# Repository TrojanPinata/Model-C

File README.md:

<div align="center">

# Model-C

### A four function calculator and numpad combo with integrated battery, power-saving, and mechanical switches

The first version of this project is stored in the `old pcb` directory, and is based off of the ATmega32A MCU. While good, I felt like the RP2040 is more realistic in terms of both cost and development overhead.

</div>

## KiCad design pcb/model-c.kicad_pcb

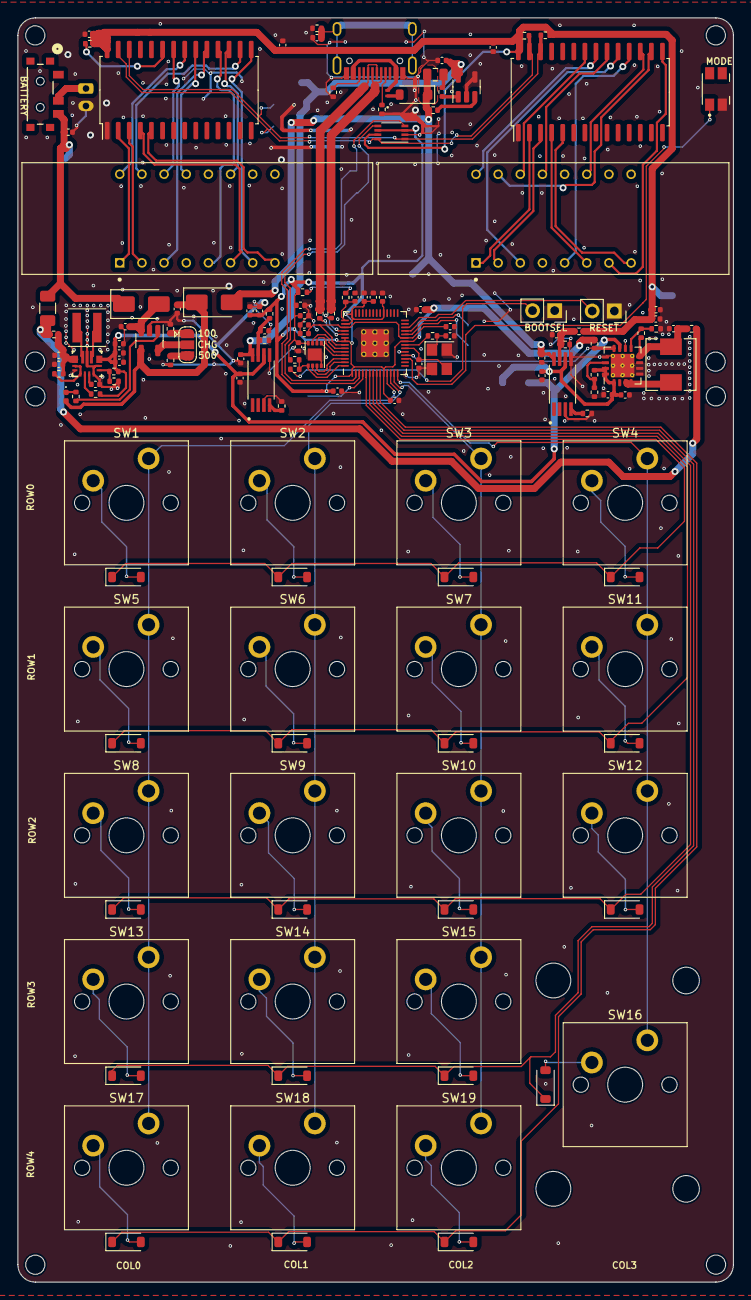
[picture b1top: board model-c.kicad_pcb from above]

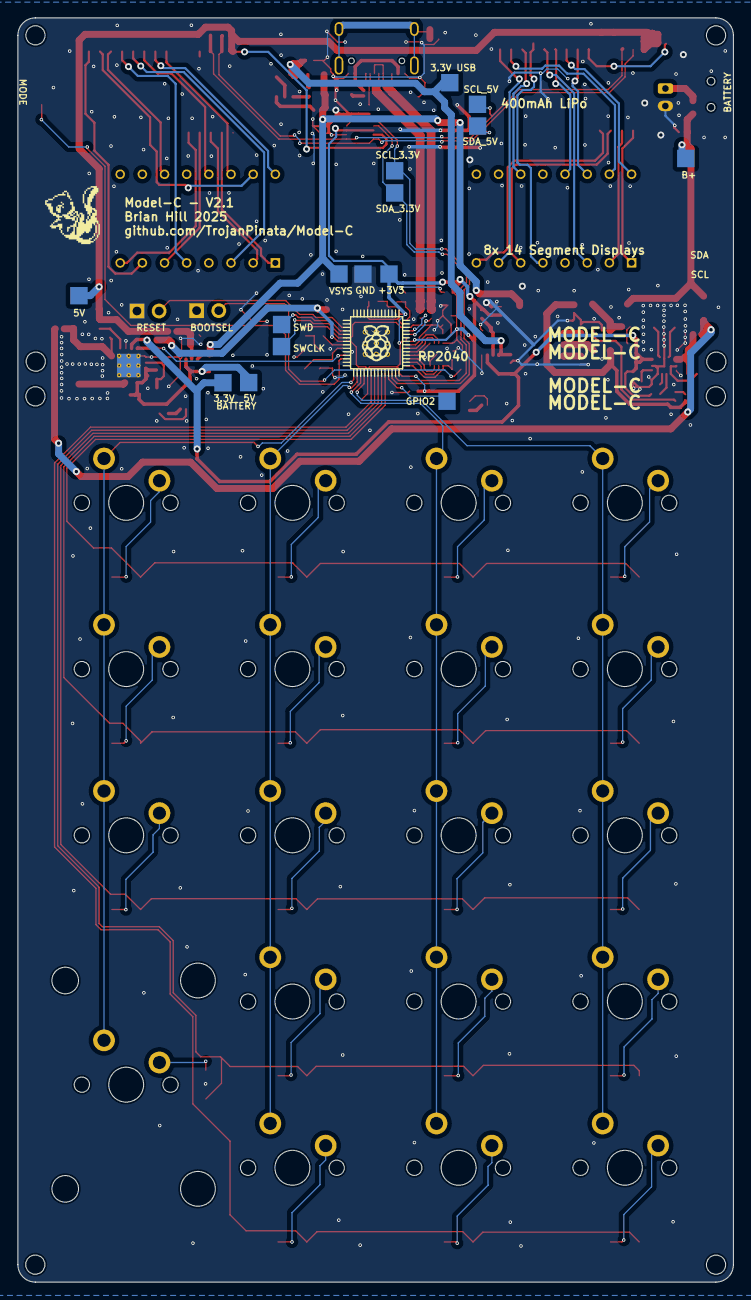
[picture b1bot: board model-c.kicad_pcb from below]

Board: 2 copper layers, 82.0 x 144.9 mm, 161 parts (16 on the bottom side), 120 nets.

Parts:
C1, C5, C6, C8, C9, C11, C12, C13, C14, C15, C16, C17, C24, C30, C31, C32, C33: 0.1uF; C_0402_1005Metric
C2, C21, C23, C25, C26, C29, C34, C37, C39, C40, C41: 10uF; C_0402_1005Metric
C3, C4: 22pF; C_0402_1005Metric
C7, C42: 1uF; C_0402_1005Metric
C10, C18: 2.2uF; C_0402_1005Metric
C19, C20, C22: 4.7uF; C_0402_1005Metric
C27, C35, C36: 22uF; C_0402_1005Metric
C28: 100uF_LowESR; C_0402_1005Metric
C38: 100nF; C_0402_1005Metric
D1, D2, D3, D4, D5, D6, D7, D8, D9, D10, D11, D12, D13, D14, D15, D16, D17, D18, D19: D; D_SOD-123
D21: 1N4002W; D_SOD-123
D22: MBRA140; D_SMA
D23: LED; LED_0402_1005Metric
D24: SS14; D_SMA
D25: TPD1E05U06; RTVS_DFN1006-2_SOD882_NEX
DS1, DS2: TDCG1060M; DISPLAY_TDCG1060M
F1: 0805L050WR; Fuse_0805_2012Metric
F2: MF-NSMF075-2; Fuse_1206_3216Metric
FB1, FB2, FB3, FB4, FB5: FB; R_0402_1005Metric
H1: Stabilizer; Stabilizer_Cherry_MX_2.00u
IC1, IC2: HTK16K33; SOP-28_7.5x17.9mm_P1.27mm
J1: Batt; JST_PH_S2B-PH-K_1x02_P2.00mm_Horizontal
J2, J3: Conn_01x02_Socket; PinSocket_1x02_P2.54mm_Vertical
JP2: 500mA - 100mA; SolderJumper-3_P1.3mm_Open_RoundedPad1.0x1.5mm
L1: 4.7uH; L_Sunlord_MWSA0503S
L2: 1.5uH; L_Coilcraft_XxL4020
R1, R3: 1k; R_0402_1005Metric
R2, R8, R16, R21, R23: 10k; R_0402_1005Metric
R4: 47k; R_0402_1005Metric
R5: 160k; R_0402_1005Metric
R6, R7: 5.1k; R_0402_1005Metric
R9, R22, R26, R27, R28, R30, R32: 100k; R_0402_1005Metric
R10: 200; R_0402_1005Metric
R11: 1; R_0402_1005Metric
R12, R13: 27; R_0402_1005Metric
R14: 330; R_0402_1005Metric
R15: 2k; R_0402_1005Metric
R24, R25, R33, R34: 4.7k; R_0402_1005Metric
R29: 316k; R_0402_1005Metric
R31: 523k; R_0402_1005Metric
S1: MODE; SW_EVQ-P7A01P
SW1, SW2, SW3, SW4, SW5, SW6, SW7, SW8, SW9, SW10, SW11, SW12, SW13, SW14, SW15, SW17, SW18, SW19: SW_SPST; SW_Cherry_MX_PCB_1.00u
SW16: SW_SPST; SW_Cherry_MX_PCB_2.00u_90deg
SW21: SW_SPDT; MK-12C02-G020_GSW
TP1, TP2, TP3, TP4, TP5, TP6, TP7, TP8, TP9, TP10, TP11, TP12, TP13, TP14, TP15: TestPoint; CustomTestPoint
U1: W25Q16JVUXIQ; SON-8-1EP_3x2mm_P0.5mm_EP1.4x1.6mm
U3: RP2040; RP2040-QFN-56
U4: MCP73831-2-OT; SOT-23-5
U5: TPS61090; Texas_S-PVQFN-N16_EP2.7x2.7mm_ThermalVias
U7: TLV75533PDBVR; SOT-23-5
U8, U9: TPS2115APW; SOP65P640X120-8N
U10: TXS0102DCU; VSSOP-8_2.3x2mm_P0.5mm
U11: TPS63070RNMR; RNM0015A
USB1: HRO-TYPE-C-31-M-12
Y1: 12MHz; Crystal_SMD_3225-4Pin_3.2x2.5mm

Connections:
+1V1: C7.1, C8.1, C9.1, U3.23 (DVDD), U3.45 (VREG_VOUT), U3.50 (DVDD)
+3V3: C1.2, C2.1, C11.1, C12.1, C13.1, C14.1, C15.1, C16.1, C17.1, C18.1, C22.1, FB3.1, R2.2, R10.1, R21.1, TP9.1, U1.8 (VCC), U3.1 (IOVDD), U3.10 (IOVDD), U3.22 (IOVDD), U3.33 (IOVDD), U3.42 (IOVDD), U3.44 (VREG_IN), U3.48 (USB_VDD), U3.49 (IOVDD), U10.3 (VCCA), U10.6 (OE)
+5V: C5.1, C21.1, C23.1, C24.1, C25.1, FB2.1, IC1.28 (VDD), IC2.28 (VDD), R4.2, R33.1, R34.2, TP11.1, U10.7 (VCCB)
/3.3V_BATT: C30.1, C39.2, C40.1, C41.2, R28.1, R29.1, TP10.1, U5.11 (EN), U8.6 (1N2), U11.7 (VOUT), U11.8 (VOUT)
/3.3V_USB: C29.1, C31.1, TP7.1, U7.5 (OUT), U8.8 (1N1)
/5V_BATT: C27.1, C28.1, C33.1, R31.2, TP8.1, U5.1 (VOUT), U5.15 (VOUT), U5.16 (VOUT), U9.6 (1N2)
/ADC_VREF: R10.2, R11.1
/B+: F2.2, FB4.2, FB5.2
/LBO: R21.2, U3.18 (GPIO15), U5.12 (LBO)
/QSPI_SCLK: U1.6 (CLK), U3.52 (QSPI_SCLK)
/QSPI_SD0: U1.5 (DI(IO0)), U3.53 (QSPI_SD0)
/QSPI_SD1: U1.2 (DO(IO1)), U3.55 (QSPI_SD1)
/QSPI_SD2: U1.3 (IO2), U3.54 (QSPI_SD2)
/QSPI_SD3: U1.7 (IO3), U3.51 (QSPI_SD3)
/QSPI_SS: R1.1, R2.1, U1.1 (~CS), U3.56 (QSPI_SS)
/RUN: J3.2, U3.26 (RUN)
/SCL_3.3V: TP15.1, U3.3 (GPIO1), U10.4 (A2)
/SCL_5V: IC1.26 (SCL), IC2.26 (SCL), R33.2, TP12.1, U10.1 (B2)
/SDA_3.3V: TP14.1, U3.2 (GPIO0), U10.5 (A1)
/SDA_5V: IC1.27 (SDA), IC2.27 (SDA), R34.1, TP13.1, U10.8 (B1)
/USB_BOOT: J2.2, R1.2
/USB_DN: R13.2, USB1.5 (DN2), USB1.7 (DN1)
/USB_DP: R12.2, USB1.6 (DP1), USB1.8 (DP2)
/XIN: C3.2, U3.20 (XIN), Y1.3
/XOUT: R3.2, U3.21 (XOUT)
/col0: SW1.2 (B), SW5.2 (B), SW8.2 (B), SW13.2 (B), SW17.2 (B), U3.11 (GPIO8)
/col1: SW2.2 (B), SW6.2 (B), SW9.2 (B), SW14.2 (B), SW18.2 (B), U3.12 (GPIO9)
/col2: SW3.2 (B), SW7.2 (B), SW10.2 (B), SW15.2 (B), SW19.2 (B), U3.13 (GPIO10)
/col3: SW4.2 (B), SW11.2 (B), SW12.2 (B), SW16.2 (B), U3.14 (GPIO11)
/mode: S1.1_1, U3.17 (GPIO14)
/row0: D1.1 (K), D2.1 (K), D3.1 (K), D4.1 (K), U3.5 (GPIO3)
/row1: D5.1 (K), D6.1 (K), D7.1 (K), D8.1 (K), U3.6 (GPIO4)
/row2: D9.1 (K), D10.1 (K), D11.1 (K), D12.1 (K), U3.7 (GPIO5)
/row3: D13.1 (K), D14.1 (K), D15.1 (K), D16.1 (K), U3.8 (GPIO6)
/row4: D17.1 (K), D18.1 (K), D19.1 (K), U3.9 (GPIO7)
GND: C1.1, C2.2, C3.1, C4.2, C5.2, C6.2, C7.2, C8.2, C9.2, C10.2, C11.2, C12.2, C13.2, C14.2, C15.2, C16.2, C17.2, C18.2, C19.2, C20.2, C21.2, C22.2, C23.2, C24.2, C25.2, C26.2, C27.2, C28.2, C29.2, C30.2, C31.2, C32.2, C33.2, C34.2, C35.2, C36.2, C37.1, C38.2, C39.1, C40.2, C41.1, C42.2, IC1.1 (VSS), IC2.1 (VSS), J1.2, J2.1, J3.1, R6.2, R7.2, R8.1, R9.2, R15.1, R16.1, R24.2, R25.2, R26.2, R27.2, R30.2, R32.1, S1.2_1, TP3.1, U1.4 (GND), U1.9 (EP), U3.19 (TESTEN), U3.57 (GND), U4.2 (V_{SS}), U5.5 (PGND), U5.6 (PGND), U5.7 (PGND), U5.10 (SYNC), U5.13 (GND), U5.17 (PAD), U7.2 (GND), U7.4 (BP), U8.3 (D1), U8.5 (GND), U9.3 (D1), U9.5 (GND), U10.2 (GND), U11.4 (GND), U11.6 (FB2), U11.10 (PGND), U11.15 (VSEL), USB1.1 (GND), USB1.12 (GND), Y1.2, Y1.4
unnamed: C4.1, R3.1, Y1.1
unnamed: C34.1, C37.2, FB5.1, R23.1, U11.12 (VIN), U11.13 (VIN)
unnamed: D1.2 (A), SW1.1 (A)
unnamed: D2.2 (A), SW2.1 (A)
unnamed: D3.2 (A), SW3.1 (A)
unnamed: D4.2 (A), SW4.1 (A)
unnamed: D5.2 (A), SW5.1 (A)
unnamed: D6.2 (A), SW6.1 (A)
unnamed: D7.2 (A), SW7.1 (A)
unnamed: D8.2 (A), SW11.1 (A)
unnamed: D9.2 (A), SW8.1 (A)
unnamed: D10.2 (A), SW9.1 (A)
unnamed: D11.2 (A), SW10.1 (A)
unnamed: D12.2 (A), SW12.1 (A)
unnamed: D13.2 (A), SW13.1 (A)
unnamed: D14.2 (A), SW14.1 (A)
unnamed: D15.2 (A), SW15.1 (A)
unnamed: D16.2 (A), SW16.1 (A)
unnamed: D17.2 (A), SW17.1 (A)
unnamed: D18.2 (A), SW18.1 (A)
unnamed: D19.2 (A), SW19.1 (A)
unnamed: D21.2 (A), D25.1 (K)
unnamed: C19.1, D22.1 (K), D23.2 (A), U4.4 (V_{DD})
unnamed: D23.1 (K), R14.1
unnamed: C42.1, D24.2 (A), U4.3 (V_{BAT})
unnamed: C20.1, D24.1 (K), F2.1, SW21.3 (C), TP5.1
unnamed: F1.2, FB1.2
unnamed: DS2.1, IC1.2 (COM0/AD)
unnamed: DS2.2, IC1.3 (COM1/KS0)
unnamed: DS2.6, IC1.4 (COM2/KS1)
unnamed: DS2.8, IC1.5 (COM3/KS2)
unnamed: DS2.14, IC1.22 (ROW3/K1)
unnamed: DS2.16, IC1.21 (ROW4/K2)
unnamed: DS2.13, IC1.20 (ROW5/K3)
unnamed: DS2.3, IC1.19 (ROW6/K4)
unnamed: DS2.5, IC1.18 (ROW7/K5)
unnamed: DS2.11, IC1.17 (ROW8/K6)
unnamed: DS2.15, IC1.16 (ROW9/K7)
unnamed: DS2.7, IC1.15 (ROW10/K8)
unnamed: DS1.1, IC2.2 (COM0/AD)
unnamed: DS1.2, IC2.3 (COM1/KS0)
unnamed: DS1.6, IC2.4 (COM2/KS1)
unnamed: DS1.8, IC2.5 (COM3/KS2)
unnamed: IC2.23 (ROW2/A0), R4.1
unnamed: DS1.14, IC2.22 (ROW3/K1)
unnamed: DS1.16, IC2.21 (ROW4/K2)
unnamed: DS1.13, IC2.20 (ROW5/K3)
unnamed: DS1.3, IC2.19 (ROW6/K4)
unnamed: DS1.5, IC2.18 (ROW7/K5)
unnamed: DS1.11, IC2.17 (ROW8/K6)
unnamed: DS1.15, IC2.16 (ROW9/K7)
unnamed: DS1.7, IC2.15 (ROW10/K8)
unnamed: J1.1, SW21.2 (B)
unnamed: JP2.1 (A), R16.2
unnamed: JP2.3 (B), R15.2
unnamed: JP2.2 (C), U4.5 (PROG)
unnamed: L1.2, U5.3 (SW), U5.4 (SW)
unnamed: C10.1, R11.2, U3.43 (ADC_AVDD)
unnamed: TP4.1, U3.4 (GPIO2)
unnamed: TP1.1, U3.24 (SWCLK)
unnamed: TP2.1, U3.25 (SWD)
unnamed: R13.1, U3.46 (USB_DM)
unnamed: R12.1, U3.47 (USB_DP)
unnamed: R14.2, U4.1 (STAT)
unnamed: R31.1, R32.2, U5.14 (FB)
unnamed: R5.2, R9.1, U5.9 (LBI)
unnamed: C26.1, FB4.1, L1.1, R5.1, U5.8 (VBAT)
unnamed: R22.2, U7.3 (EN)
unnamed: FB1.1, U7.1 (IN)
unnamed: R25.1, U8.4 (ILIM)
unnamed: C35.1, FB3.2, R26.1, U8.7 (OUT)
unnamed: R24.1, U9.4 (ILIM)
unnamed: C36.1, FB2.2, R27.1, U9.7 (OUT)
unnamed: R23.2, U11.1 (PS_SYNC), U11.14 (EN)
unnamed: R29.2, R30.1, U11.5 (FB)
unnamed: L2.1, U11.11 (L1)
unnamed: L2.2, U11.9 (L2)
unnamed: R28.2, U11.2 (PG)
unnamed: C38.1, U11.3 (VAUX)
unnamed: R6.1, USB1.4 (CC1)
unnamed: R7.1, USB1.10 (CC2)
unnamed: C6.1, R8.2, USB1.13 (SHIELD)
VBUS: D25.2 (A), USB1.2 (VBUS), USB1.11 (VBUS)
VSYS: C32.1, D21.1 (K), D22.2 (A), F1.1, R22.1, TP6.1, U9.8 (1N1)

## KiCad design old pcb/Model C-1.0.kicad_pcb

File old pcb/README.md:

# Why does this exist?

I am leaving this design here because I think it is a good representation of where I started from and what I am capable now.

This project has been refined and I feel the current design is much more cost efficient and useful.

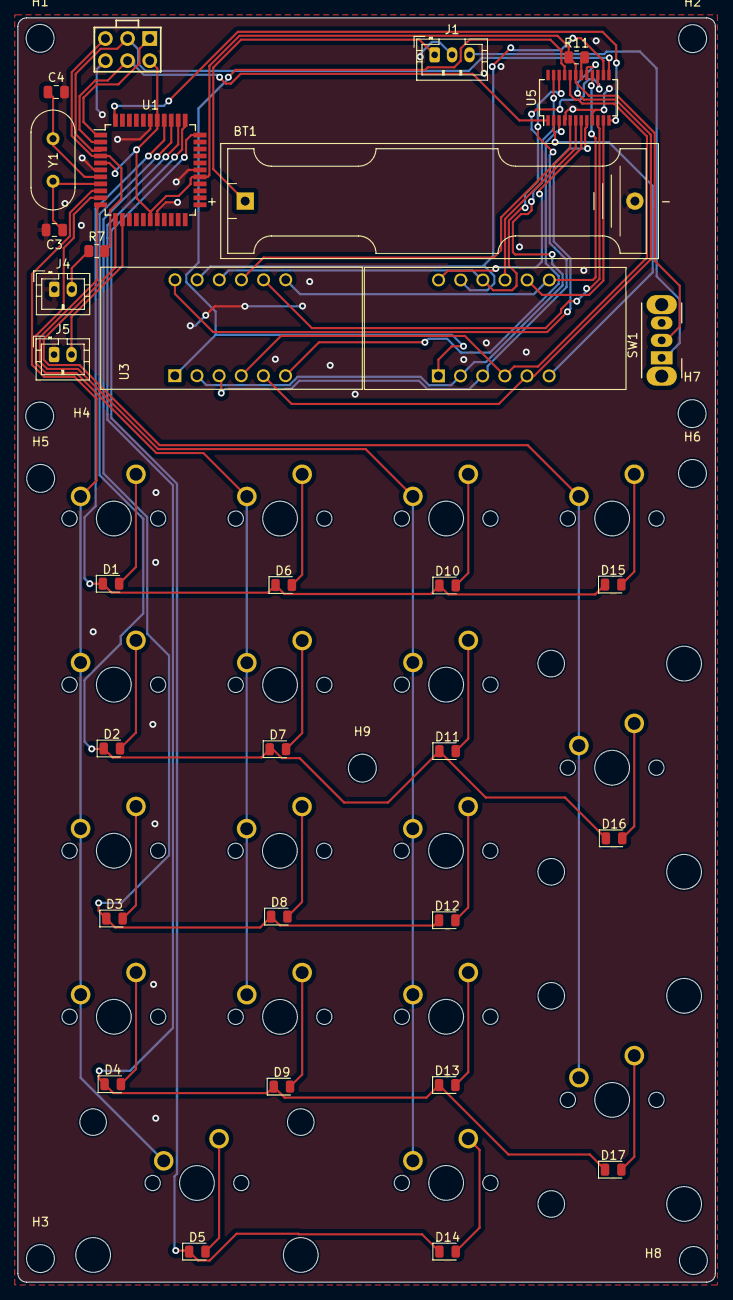
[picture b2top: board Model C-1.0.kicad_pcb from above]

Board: 2 copper layers, 80.0 x 145.0 mm, 58 parts (0 on the bottom side), 56 nets.

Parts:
BT1: Battery_Cell; BatteryHolder_Keystone_2466_1xAAA
C3, C4: 22p; C_0805_2012Metric
D1, D2, D3, D4, D5, D6, D7, D8, D9, D10, D11, D12, D13, D14, D15, D16, D17: D; D_0805_2012Metric
H1, H2, H3, H4, H5, H6, H7, H8, H9: MountingHole; MountingHole_3.2mm_M3
J1: 1.5V-5V Boost Converter; JST_PH_B3B-PH-K_1x03_P2.00mm_Vertical
J3: AVR-ISP-6; AVR_ICSP_3x2
J4: reset; JST_PH_B2B-PH-K_1x02_P2.00mm_Vertical
J5: boot; JST_PH_B2B-PH-K_1x02_P2.00mm_Vertical
R7: 10k; R_0805_2012Metric
R11: 12k; R_0805_2012Metric
SW1: SW_SPST; SW_CuK_OS102011MA1QN1_SPDT_Angled
SW-1U-1, SW-1U-2, SW-1U-3, SW-1U-4, SW-1U-5, SW-1U-6, SW-1U-7, SW-1U-8, SW-1U-9, SW-1U-10, SW-1U-11, SW-1U-12, SW-1U-13, SW-1U-14: KEYSW; MXOnly-1U-NoLED
SW-2U-1: KEYSW; MXOnly-2U-NoLED
SW-2U-2, SW-2U-3: KEYSW; MXOnly-2U-VerticalStabilizers-NoLED
U1: ATmega32A-A; TQFP-44_10x10mm_P0.8mm
U3, U4: CA56-12CGKWA
U5: MAX7219; SSOP-24_3.9x8.7mm_P0.635mm
Y1: Crystal; Crystal_HC49-4H_Vertical

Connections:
+5V: J1.3, SW1.1 (A)
/0: U4.6 (CA4), U5.2 (DIG_0)
/1: U4.8 (CA3), U5.11 (DIG_1)
/2: U4.9 (CA2), U5.6 (DIG_2)
/3: U4.12 (CA1), U5.7 (DIG_3)
/4: U3.6 (CA4), U5.3 (DIG_4)
/5: U3.8 (CA3), U5.10 (DIG_5)
/5v switched: J3.2 (VCC), R11.1, SW1.2 (B), U1.5 (VCC), U1.17 (VCC), U1.27 (AVCC), U1.38 (VCC), U5.19 (V+)
/6: U3.9 (CA2), U5.5 (DIG_6)
/7: U3.12 (CA1), U5.8 (DIG_7)
/a: U3.11 (a), U4.11 (a), U5.14 (SEG_A)
/b: U3.7 (b), U4.7 (b), U5.16 (SEG_B)
/boot: J5.2, U1.13 (PD4)
/c: U3.4 (c), U4.4 (c), U5.20 (SEG_C)
/col0: SW-1U-1.1, SW-1U-2.1, SW-1U-3.1, SW-1U-4.1, SW-2U-1.1, U1.9 (PD0)
/col1: SW-1U-5.1, SW-1U-6.1, SW-1U-7.1, SW-1U-8.1, U1.10 (PD1)
/col2: SW-1U-9.1, SW-1U-10.1, SW-1U-11.1, SW-1U-12.1, SW-1U-13.1, U1.11 (PD2)
/col3: SW-1U-14.1, SW-2U-2.1, SW-2U-3.1, U1.12 (PD3)
/d: U3.2 (d), U4.2 (d), U5.23 (SEG_D)
/dp: U3.3 (DPX), U4.3 (DPX), U5.22 (SEG_DP)
/e: U3.1 (e), U4.1 (e), U5.21 (SEG_E)
/f: U3.10 (f), U4.10 (f), U5.15 (SEG_F)
/g: U3.5 (g), U4.5 (g), U5.17 (SEG_G)
/miso: J3.1 (MISO), U1.1 (PB5)
/mosi: J3.4 (MOSI), U1.2 (PB6), U5.1 (DIN)
/reset: J3.5 (~RST), R7.2, U1.4 (~RESET)
/row0: D1.1, D6.1, D10.1, D15.1, U1.37 (PA0)
/row1: D2.1, D7.1, D11.1, D16.1, U1.36 (PA1)
/row2: D3.1, D8.1, D12.1, U1.35 (PA2)
/row3: D4.1, D9.1, D13.1, D17.1, U1.34 (PA3)
/row4: D5.1, D14.1, U1.33 (PA4)
/sck: J3.3 (SCK), U1.3 (PB7), U5.13 (CLK)
/ssg: U1.44 (PB4), U5.12 (LOAD)
GND: BT1.2 (-), C3.2, C4.2, J1.2, J3.6 (GND), J4.1, J5.1, U1.6 (GND), U1.18 (GND), U1.28 (GND), U1.39 (GND), U5.4 (GND), U5.9 (GND)
unnamed: BT1.1 (+), J1.1
unnamed: D1.2, SW-1U-1.2
unnamed: D2.2, SW-1U-2.2
unnamed: D3.2, SW-1U-3.2
unnamed: D4.2, SW-1U-4.2
unnamed: D5.2, SW-2U-1.2
unnamed: D6.2, SW-1U-5.2
unnamed: D7.2, SW-1U-6.2
unnamed: D8.2, SW-1U-7.2
unnamed: D9.2, SW-1U-8.2
unnamed: D10.2, SW-1U-9.2
unnamed: D11.2, SW-1U-10.2
unnamed: D12.2, SW-1U-11.2
unnamed: D13.2, SW-1U-12.2
unnamed: D14.2, SW-1U-13.2
unnamed: D15.2, SW-1U-14.2
unnamed: D16.2, SW-2U-2.2
unnamed: D17.2, SW-2U-3.2
unnamed: J4.2, R7.1
unnamed: C3.1, U1.8 (XTAL1), Y1.1
unnamed: C4.1, U1.7 (XTAL2), Y1.2
unnamed: R11.2, U5.18 (ISET)

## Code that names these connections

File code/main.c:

#include <avr/io.h>
#include <LedControl.h>

#define COL_PORT PORTD
#define COL_PIN PIND
#define COL_DDR DDRD

#define ROW_PORT PORTA
#define ROW_PIN PINA
#define ROW_DDR DDRA

#define MAX7219_PORT PORTB
#define MAX7219_DDR DDRB

#define MAX7219_SS 4 
#define MAX7219_MISO 6 
#define MAX7219_MOSI 5 
#define MAX7219_SCK 7 

// define ports
DDRA = 0x1F;
DDRB = 0x00;
DDRC = 0x00;
DDRD = 0x0F;

// define pins
int col0 = PIND0;
int col1 = PIND1;
int col2 = PIND2;
int col3 = PIND3;
int row0 = PINA0;
int row1 = PINA1;
int row2 = PINA2;
int row3 = PINA3;
int row4 = PINA4;

// define variables
double input1 = 0;
double input2 = 0;
int operator = 0;
int dotstate = 0;
double result = 0;
int decDivider = 1;

// prototypes
void display(double num);
int checkKeys();
double calc();
int isOperator();
void updateOperator();
void clear();
int stage0();
int stage1();
int stage2();
int stageSelect(int stage);
void initMCU();
void initSSG();

// main
int main() {
   int stage = 0;
   while (1) {
      stage = stageSelect(stage);
   }
}

void initMCU() {
   COL_DDR |= (1 << 0) | (1 << 1) | (1 << 2) | (1 << 3);
   ROW_DDR &= ~((1 << 0) | (1 << 1) | (1 << 2) | (1 << 3) | (1 << 4)); // Use pull-up resistors

   // Set up SPI for communication with MAX7219
   MAX7219_DDR |= (1 << MAX7219_SS) | (1 << MAX7219_MOSI) | (1 << MAX7219_SCK);
   SPCR = (1 << SPE) | (1 << MSTR) | (1 << SPR0);
}

void initSSG() {
   MAX7219_PORT |= (1 << MAX7219_SS);
}

int stageSelect(int stage) {
   if (stage == 0) {
      stage = stage0();
   }
   if (stage == 1) {
      stage = stage1();
   }
   if (stage == 2) {
      stage = stage2();
   }
   return stage;
}

int stage0() {
   int key = checkKeys();
   if (dotstate == 0 && key != -1) {   // default
      input1 = (input1 * 10) + key;
      display(input1);
   }
   else if (dotstate == 1 && key != -1) { // decimal place
      decDivider = decDivider / 10;
      input1 = input1 + (key / decDivider);
   }
   if (isOperator()) {  // operator has been selected, move to second input
      updateOperator();
      dotstate = 0;
      return 1;
   }
   if (col3 && row4) {  // enter key pressed
      operator = 0;
      dotstate = 0;
      return 2;
   }
   if (col0 && row0) {  // clear
      clear();
      return 1;
   }
   return 0
}

int stage1() {
   int key = checkKeys();
   if (dotstate == 0 && key != -1) {         // default
      input2 = (input2 * 10) + key;
      display(input2);
   }
   else if (dotstate == 1 && key != -1) {    // decimal place
      decDivider = decDivider / 10;
      input2 = input2 + (key / decDivider);
   }
   if (isOperator()) {  // do operation on current input and do another one with a new number
      input1 = calc();
      updateOperator();
      dotstate = 0;
      input2 = 0;
   }
   if (col3 && row4) {  // enter - move to stage 2
      operator = 0;
      dotstate = 0;
      return 2;
   }
   if (col0 && row0) {  // clear 
      clear();
      return 0;
   }
   return 1;
}

int stage2() {
   input1 = calc();
   if (isOperator) { // do operation on result
      updateOperator();
      return 1;
   }
   if (col3 && row4) {  // repeat operation
      input1 = calc();
   }
   int key = checkKeys();
   if (key != -1) {    // new key is pressed - delete previous result and reset
      input1 = key;
      input2 = 0;
      operator = 0;
      return 0;
   }
   dotstate = 0;
   return 2;
}

// display number
void display(double num) {
   // contact MAX7219 via SPI
}

// check if key is pressed
int checkKeys() {
   if (col0 && row3) {
      return 1;
   }
   if (col1 && row3) {
      return 2;
   }
   if (col2 && row3) {
      return 3;
   }
   if (col0 && row2) {
      return 4;
   }  
   if (col1 && row2) {
      return 5;
   }
   if (col2 && row2) {
      return 6;
   }
   if (col0 && row1) {
      return 7;
   }
   if (col1 && row1) {
      return 8;
   }
   if (col2 && row1) {
      return 9;
   }
   if (col0 && row4) {
      return 0;
   }
   if (col3 && row4) {
      dotstate = 1;
   }
   return -1;
}

// do calculation on inputs and display
double calc() {
   if (operator == 0) {
      result = input1 + input2;
   }
   if (operator == 1) {
      result = input1 - input2;
   }
   if (operator == 2) {
      result = input1 * input2;
   }
   if (operator == 3) {
      result = input1 / input2;
   }
   input1 = result;
   display(result);
   return result;
}

// check if operator key is pressed
int isOperator() {
   if ((col3 && row1) || (col3 && row0) || (col2 && row0) || (col1 && row0)) {
      return 1;
   }
   return 0;
}

// change operator state
void updateOperator() {
   if (col3 && row1) {
      operator = 0;
   }
   if (col3 && row0) {
      operator = 1;
   }
   if (col2 && row0) {
      operator = 2;
   }
   if (col1 && row0) {
      operator = 3;
   }
}

// clear all registers
void clear() {
   input1 = 0;
   operator = 0;
   result = 0;
   input2 = 0;
   display(0);
}

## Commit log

2023-10-20 oh no please don't do this to yourself
2023-10-26 swap battery
2023-10-28 minor modifications
2023-10-31 better pcb with the right components - maybe final?
2023-11-15 mounting holes + clean drc
2023-11-15 added image
2024-05-17 add license
    I have to add licenses to all of my repos bc people are stealing some of them and selling them (╥﹏╥)
2025-01-10 restarting project
2025-01-20 new pcb based on rp2040 - uses 8x 14 segment displays with mode switch - functionality extended to numpad + calculator w/ battery
2025-01-26 fixed power switch, mode button, updated readme, panelized, and added much better styling
2025-03-30 starting with numpad
2025-04-05 not working, but compiling
2025-04-06 getting scanning working in both interrupt and polling modes
2025-04-06 calculator logic complete, untested
2025-05-16 updating power system for automatic switching
2025-05-17 fixing battery charger from backfeeding, battery 3.3V regulation, 5V boost converter, and power multiplexing
2025-05-21 housing complete and PCB validated. need further validation and revisions of housing, as well as BOM to continue. updated PCB to rev. 2.1
2025-06-28 updates to pcb and addition of display code. I may rewrite the calculator code
2025-07-17 redesigned entire calculator program and added display logic
